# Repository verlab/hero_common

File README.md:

# HeRo: An Open Platform for Robotics Research and Education
<p align="justify">
Welcome to the HeRo project! This initiative introduces an innovative platform tailored for swarm robotics applications. It boasts affordability, ease of assembly using readily available components, and seamless integration with the industry-standard ROS (Robot Operating System). Our robotic platform is fully open-source, featuring a 3D-printed body coupled with open-source software. Within this repository, you'll discover a comprehensive range of ROS packages, firmware, simulations, examples, as well as additional resources such as CAD files, 3D models, schematics, and more.
</p>

For more in-depth information, please visit our documentation page [here](https://verlab.github.io/hero_common/).

## Authors

## Contributing
We welcome and appreciate contributions from the community. If you have ideas, bug fixes, or enhancements you'd like to propose, please feel free to open an issue or submit a pull request. Together, we can make HeRo an even better platform for robotics enthusiasts and researchers.

Thank you 🙏 to all our contributors!

## License
<br />This work is licensed under a <a rel="license" href="http://creativecommons.org/licenses/by-nc-nd/4.0/">Creative Commons Attribution-NonCommercial-ShareALike 4.0 International License</a>.

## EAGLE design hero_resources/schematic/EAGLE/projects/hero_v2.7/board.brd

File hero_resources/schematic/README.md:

# HeRo: An Open Platform for Robotics Research and Education

This project contributes to an open source ROS-based framework for swarm robotics. We propose an low cost, high availability swarm system that could be printed and assembled multiple times without special knowledge or hardware skills.

# Authors:
- [Paulo Rezeck](https://github.com/rezeck)
- [Maurício Ferrari](https://github.com/mauferrari)

# PCB Manufacturer

If you intend to maker the PCB by yourself, see the PCB version 2.1. These versions are simplified to make easy to developed it.

Case you intend to order the PCB from a professional manufacturer, look for the most recent version.

# Version Description

## v2.1
- Uses pinholes as vias, since it is dificult to produce vias in homemade PCB.
- Fix inconsistency 

## v2.3
- Change pinholes to vias, since we intent to order this board from PCB manufacturer.
- Fix motor conectors position

## v2.4
- Added battery charge module (TP4056)
- Update silk

## v2.5
- Change darlington-pair to mosfet

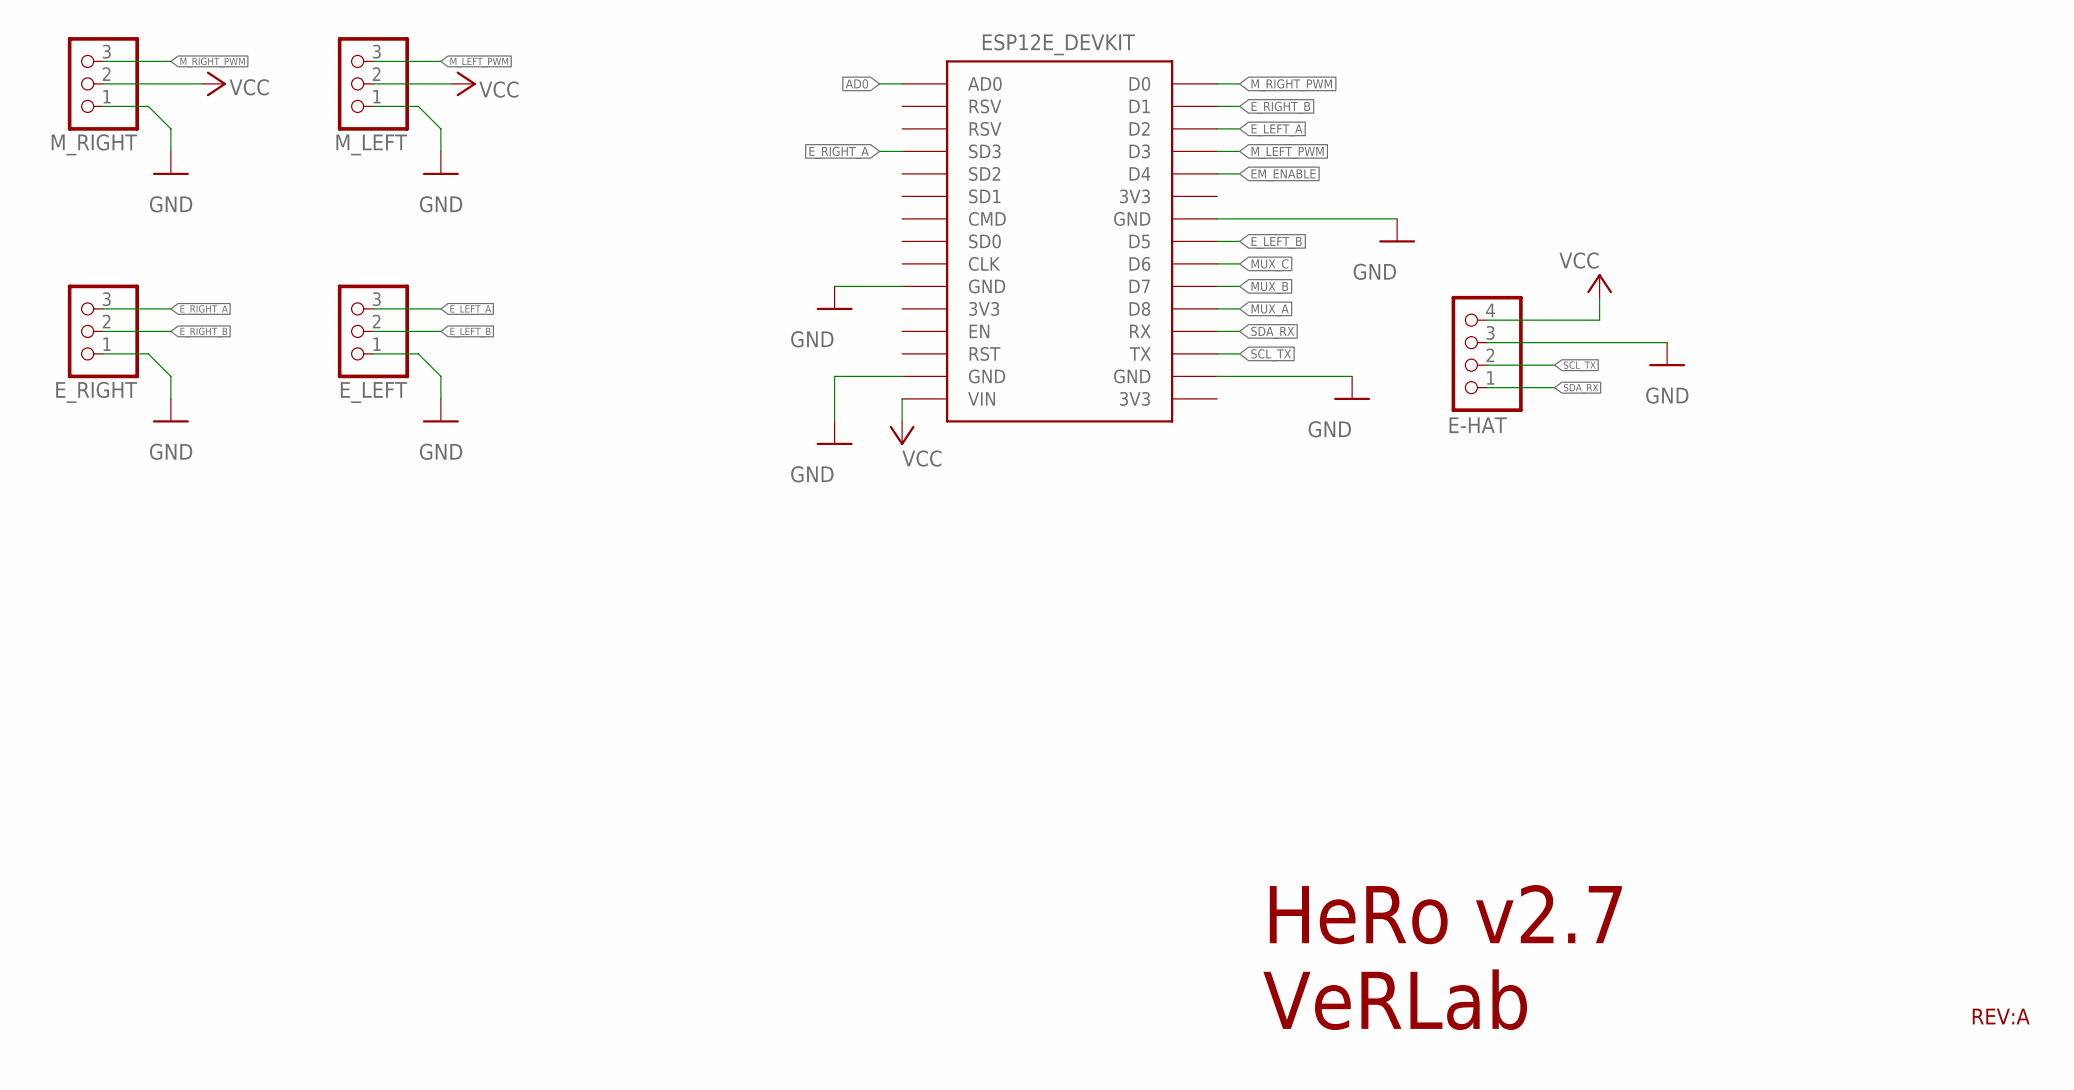
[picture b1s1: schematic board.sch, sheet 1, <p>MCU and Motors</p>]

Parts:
E-HAT: PINHD-1X4; 1X04
ESP-12E: ESP12E_DEVKIT
E_LEFT: PINHD-1X3; 1X03
E_RIGHT: PINHD-1X3; 1X03
M_LEFT: PINHD-1X3; 1X03
M_RIGHT: PINHD-1X3; 1X03

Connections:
AD0: ESP-12E.AD0; also elsewhere on the board
EM_ENABLE: ESP-12E.D4; also elsewhere on the board
E_LEFT_A: ESP-12E.D2, E_LEFT.3
E_LEFT_B: ESP-12E.D5, E_LEFT.2
E_RIGHT_A: ESP-12E.SD3, E_RIGHT.3
E_RIGHT_B: ESP-12E.D1, E_RIGHT.2
GND: E-HAT.3, ESP-12E.GND@0 (GND), ESP-12E.GND@1 (GND), ESP-12E.GND@2 (GND), ESP-12E.GND@3 (GND), E_LEFT.1, E_RIGHT.1, M_LEFT.1, M_RIGHT.1; also elsewhere on the board
MUX_A: ESP-12E.D8; also elsewhere on the board
MUX_B: ESP-12E.D7; also elsewhere on the board
MUX_C: ESP-12E.D6; also elsewhere on the board
M_LEFT_PWM: ESP-12E.D3, M_LEFT.3
M_RIGHT_PWM: ESP-12E.D0, M_RIGHT.3
SCL_TX: E-HAT.2, ESP-12E.TX
SDA_RX: E-HAT.1, ESP-12E.RX

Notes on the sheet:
HeRo v2.7 VeRLab
REV:A

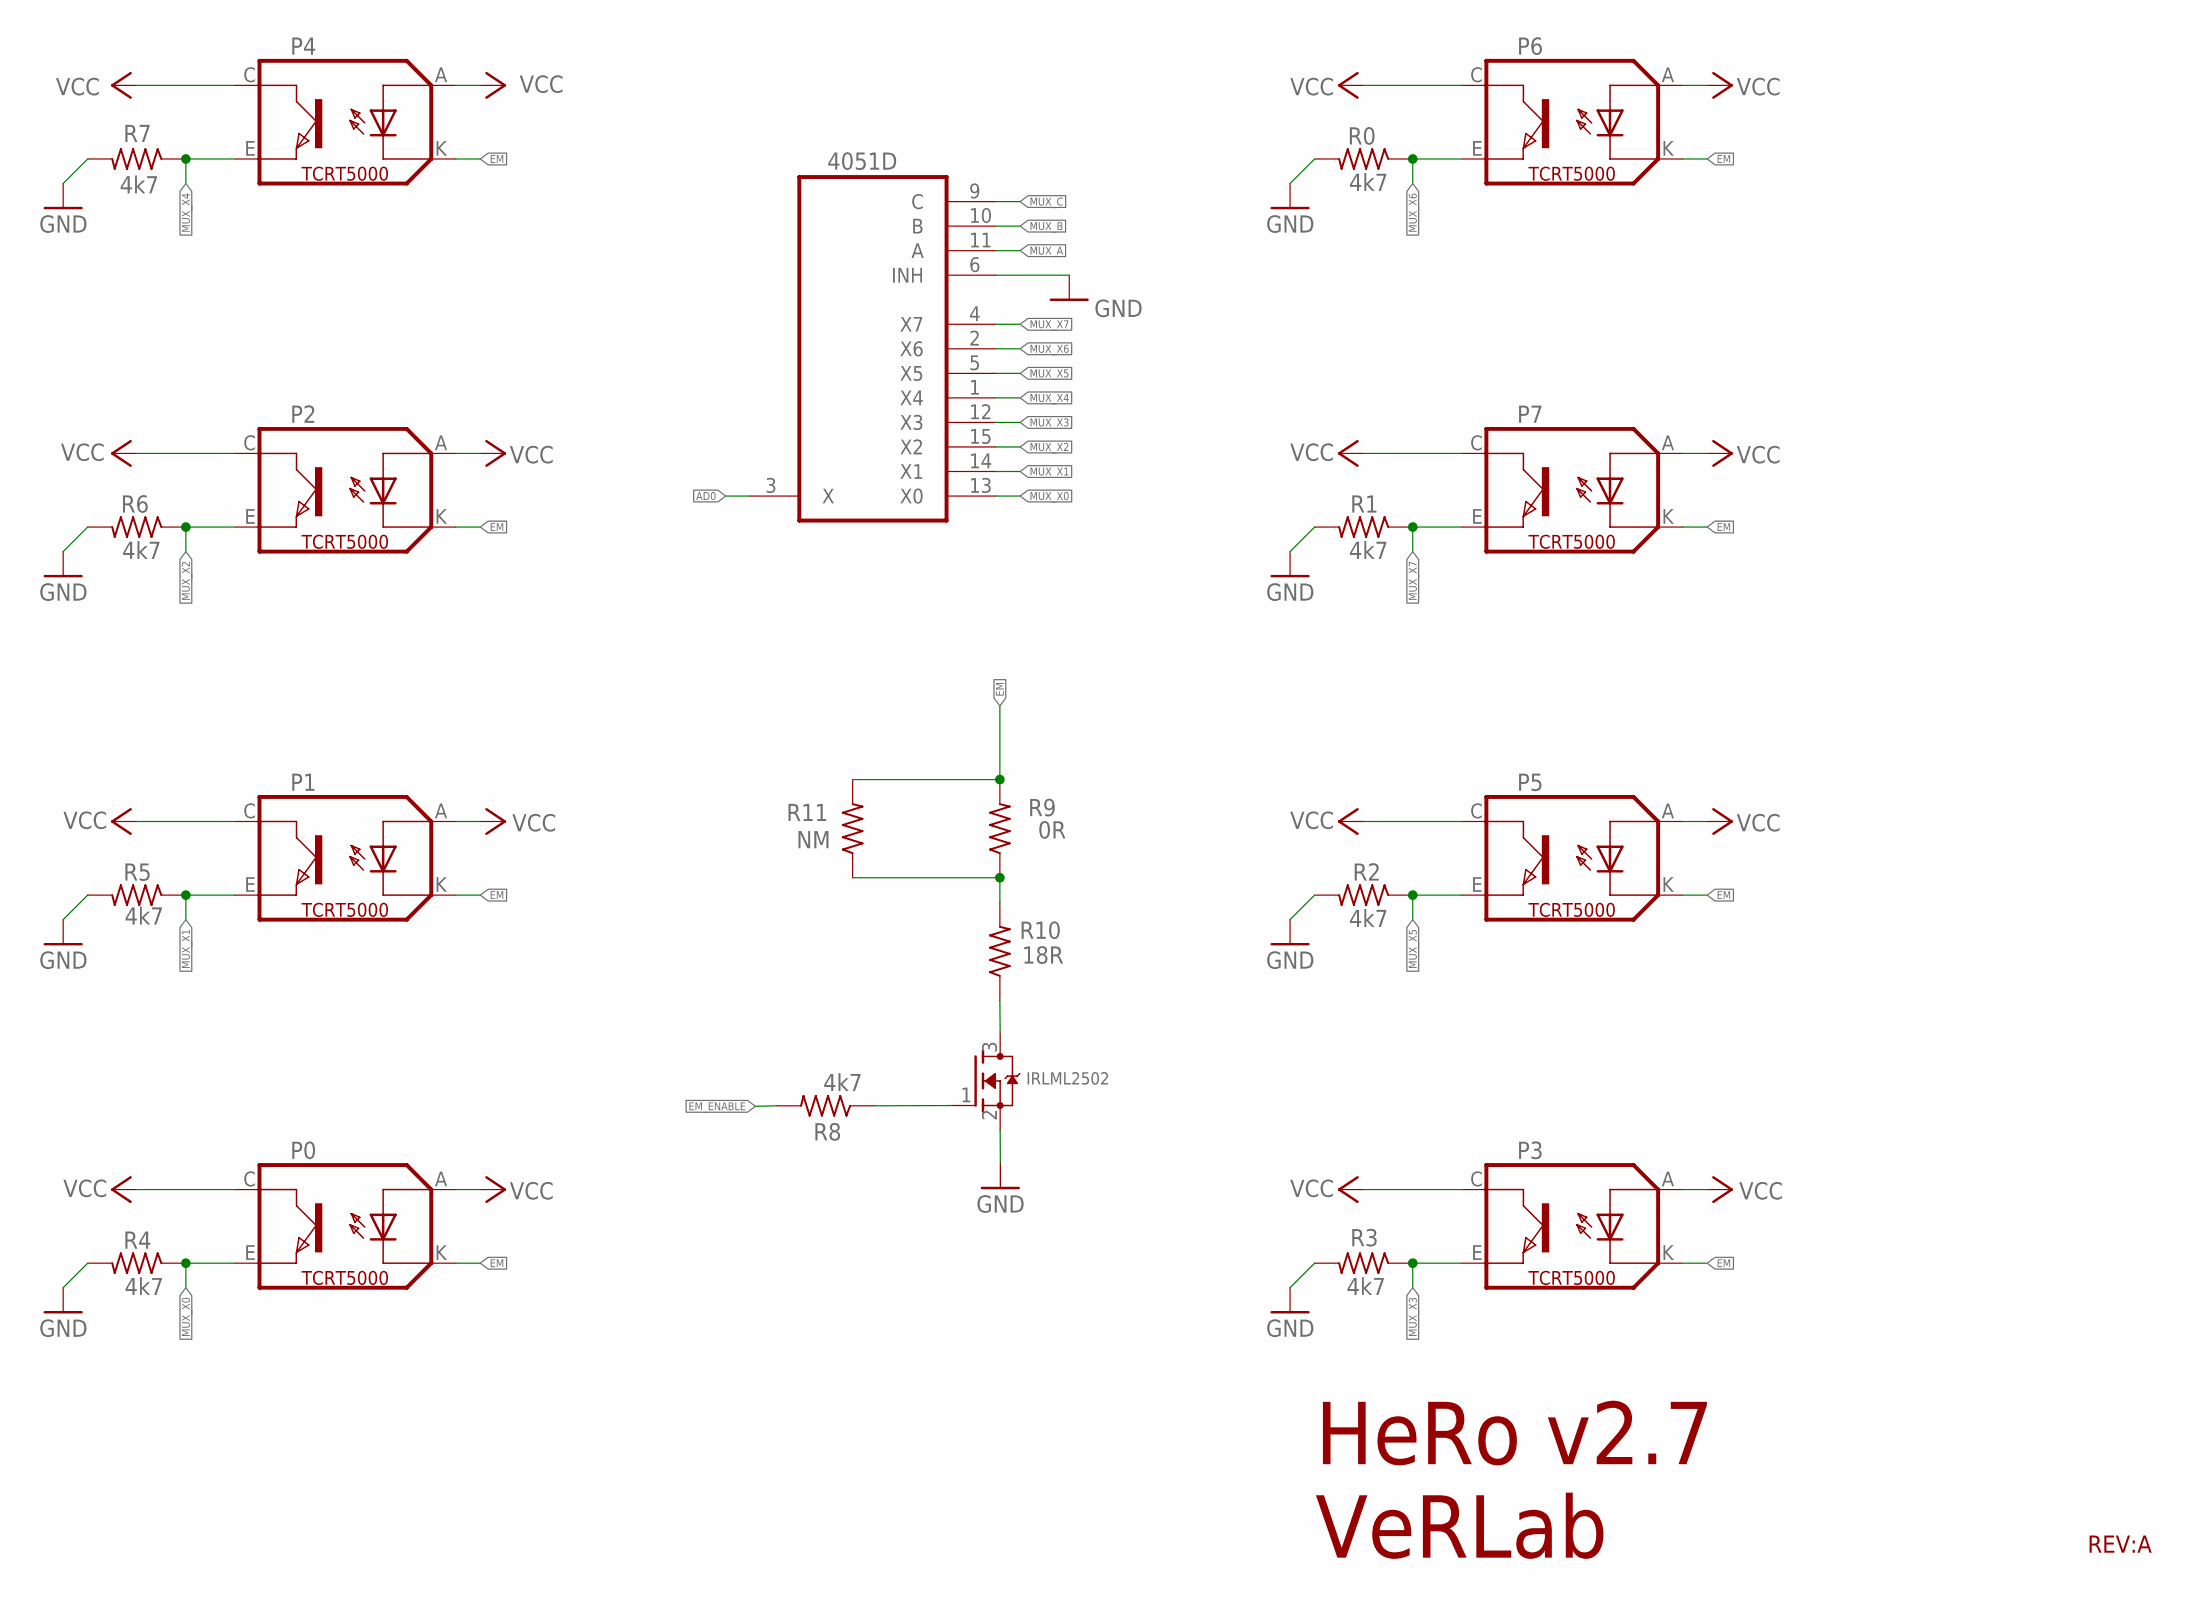
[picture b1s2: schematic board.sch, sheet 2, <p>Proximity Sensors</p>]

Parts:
IRLML2502: MOSFET-NREFLOW; SOT23
MUX: 4051D; SO16
P0, P1, P2, P3, P4, P5, P6, P7: TCRT5000
R0, R1, R2, R3, R4, R5, R6, R7: 4k7; M0805
R8: 4k7; R0805
R9: 0R; R0805
R10: 18R; R0805
R11: NM; R0805

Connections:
AD0: MUX.3 (X); also elsewhere on the board
EM: P0.K (CATHODE), P1.K (CATHODE), P2.K (CATHODE), P3.K (CATHODE), P4.K (CATHODE), P5.K (CATHODE), P6.K (CATHODE), P7.K (CATHODE), R9.2, R11.2
EM_ENABLE: R8.2; also elsewhere on the board
GND: IRLML2502.2 (S), MUX.6 (INH), MUX.7 (VEE), MUX.8 (GND), R0.2, R1.2, R2.2, R3.2, R4.2, R5.2, R6.2, R7.2; also elsewhere on the board
MUX_A: MUX.11 (A); also elsewhere on the board
MUX_B: MUX.10 (B); also elsewhere on the board
MUX_C: MUX.9 (C); also elsewhere on the board
MUX_X0: MUX.13 (X0), P0.E (EMITTER), R4.1
MUX_X1: MUX.14 (X1), P1.E (EMITTER), R5.1
MUX_X2: MUX.15 (X2), P2.E (EMITTER), R6.1
MUX_X3: MUX.12 (X3), P3.E (EMITTER), R3.1
MUX_X4: MUX.1 (X4), P4.E (EMITTER), R7.1
MUX_X5: MUX.5 (X5), P5.E (EMITTER), R2.1
MUX_X6: MUX.2 (X6), P6.E (EMITTER), R0.1
MUX_X7: MUX.4 (X7), P7.E (EMITTER), R1.1
unnamed: IRLML2502.3 (D), R10.1
unnamed: R9.1, R10.2, R11.1
unnamed: IRLML2502.1 (G), R8.1

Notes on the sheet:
HeRo v2.7 VeRLab
REV:A

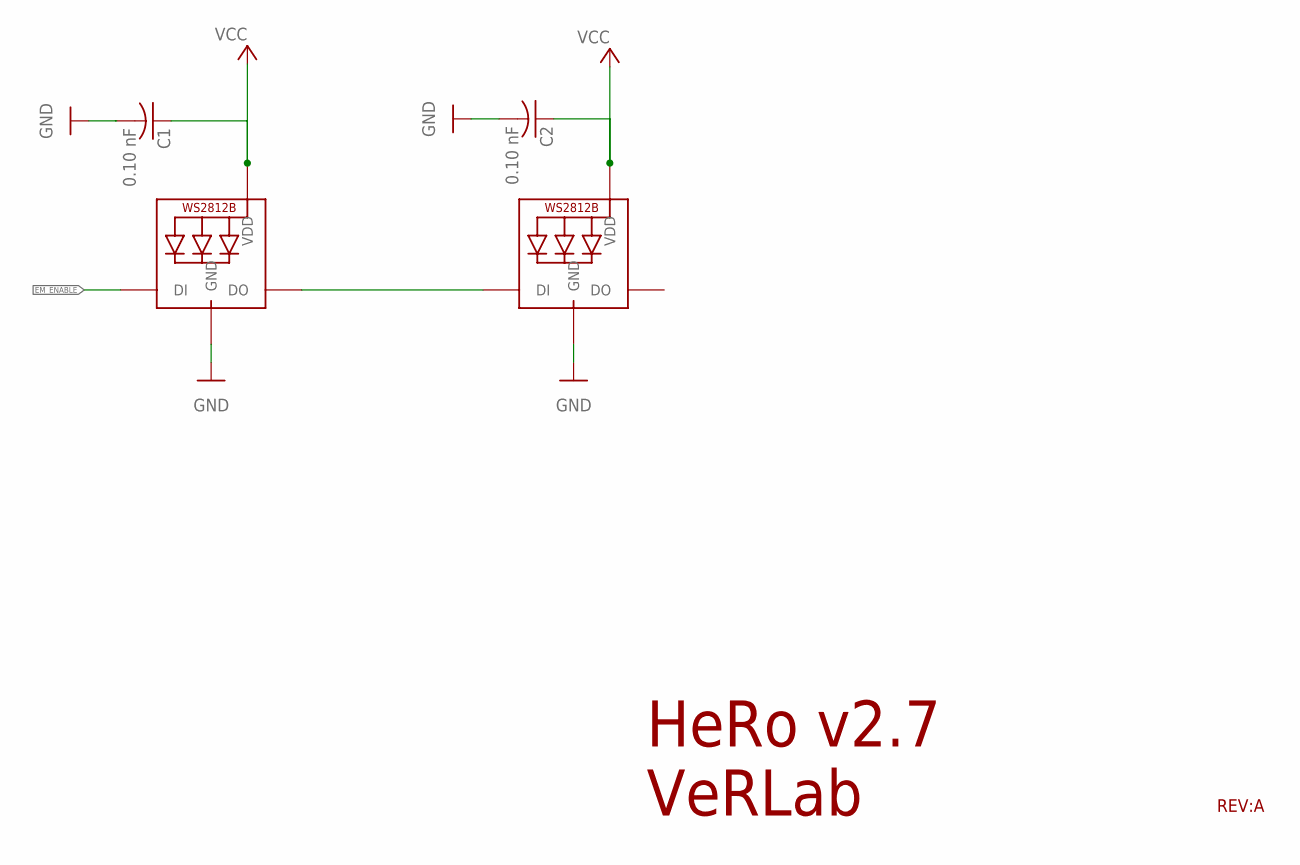
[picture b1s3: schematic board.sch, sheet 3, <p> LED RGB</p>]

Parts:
C1, C2: 0.10 nF; C0603
LED0, LED1: WS2812B5050; WS2812B

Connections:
EM_ENABLE: LED0.4-DIN (DI); also elsewhere on the board
GND: C1.2, C2.2, LED0.3-GND (GND), LED1.3-GND (GND); also elsewhere on the board
WS_OUT: LED0.2-DOUT (DO), LED1.4-DIN (DI)

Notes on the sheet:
HeRo v2.7 VeRLab
REV:A

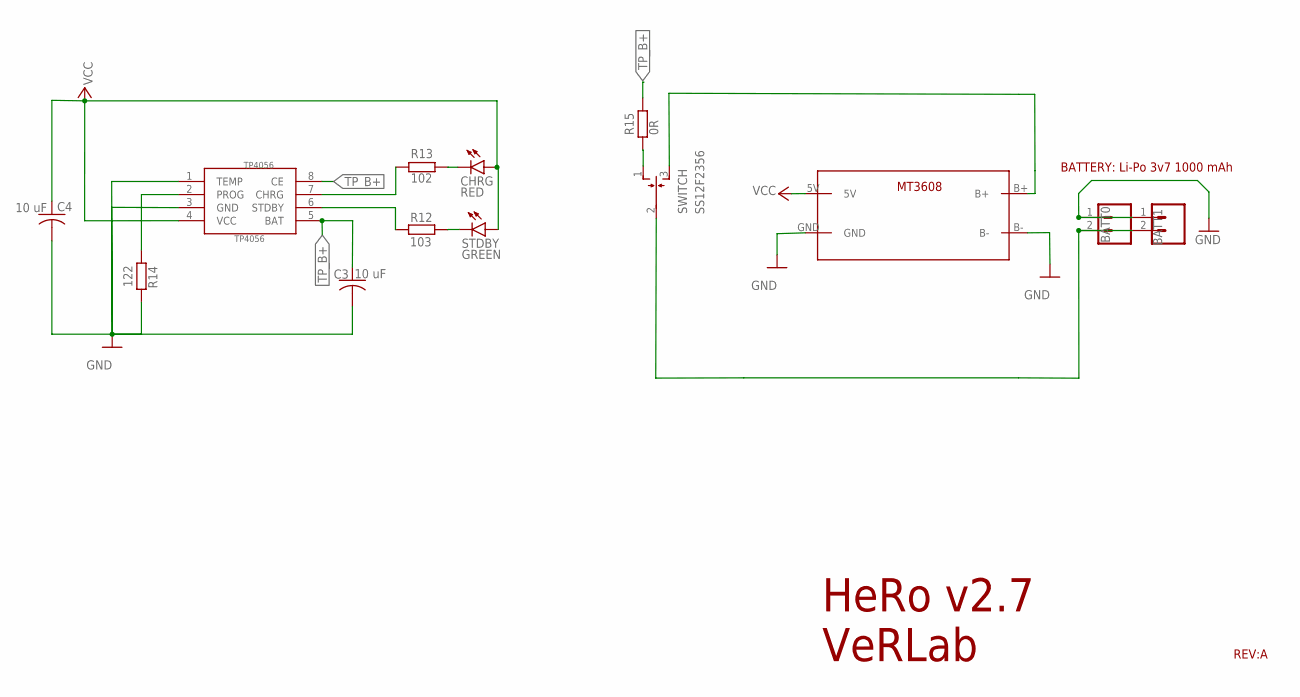
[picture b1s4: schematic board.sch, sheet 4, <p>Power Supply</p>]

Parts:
BATT0, BATT1: CONN_02JST-PTH-2; JST-2-PTH
C3, C4: 10 uF; C0603
CHRG: RED; SML0805
MT3608: MT3608
R12: 103; R0805
R13: 102; R0805
R14: 122; R0603
R15: 0R; R0805
STDBY: GREEN; SML0805
SWITCH: SS12F2356; HH3T90
TP4056: TP4056; SOP-8

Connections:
B+: MT3608.B+, SWITCH.3 (S)
CHRG: R13.1, TP4056.7 (CHRG)
GND: BATT0.1, BATT1.1, C3.2, C4.2, MT3608.B-, MT3608.GND, R14.1, TP4056.1 (TEMP), TP4056.3 (GND); also elsewhere on the board
unnamed: BATT0.2, BATT1.2, SWITCH.2
unnamed: CHRG.C, R13.2
unnamed: R12.2, STDBY.C
PROG: R14.2, TP4056.2 (PROG)
STDBY: R12.1, TP4056.6 (STDBY)
TP_BS: R15.1, SWITCH.1 (O)

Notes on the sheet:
HeRo v2.7 VeRLab
BATTERY: Li-Po 3v7 1000 mAh
REV:A

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
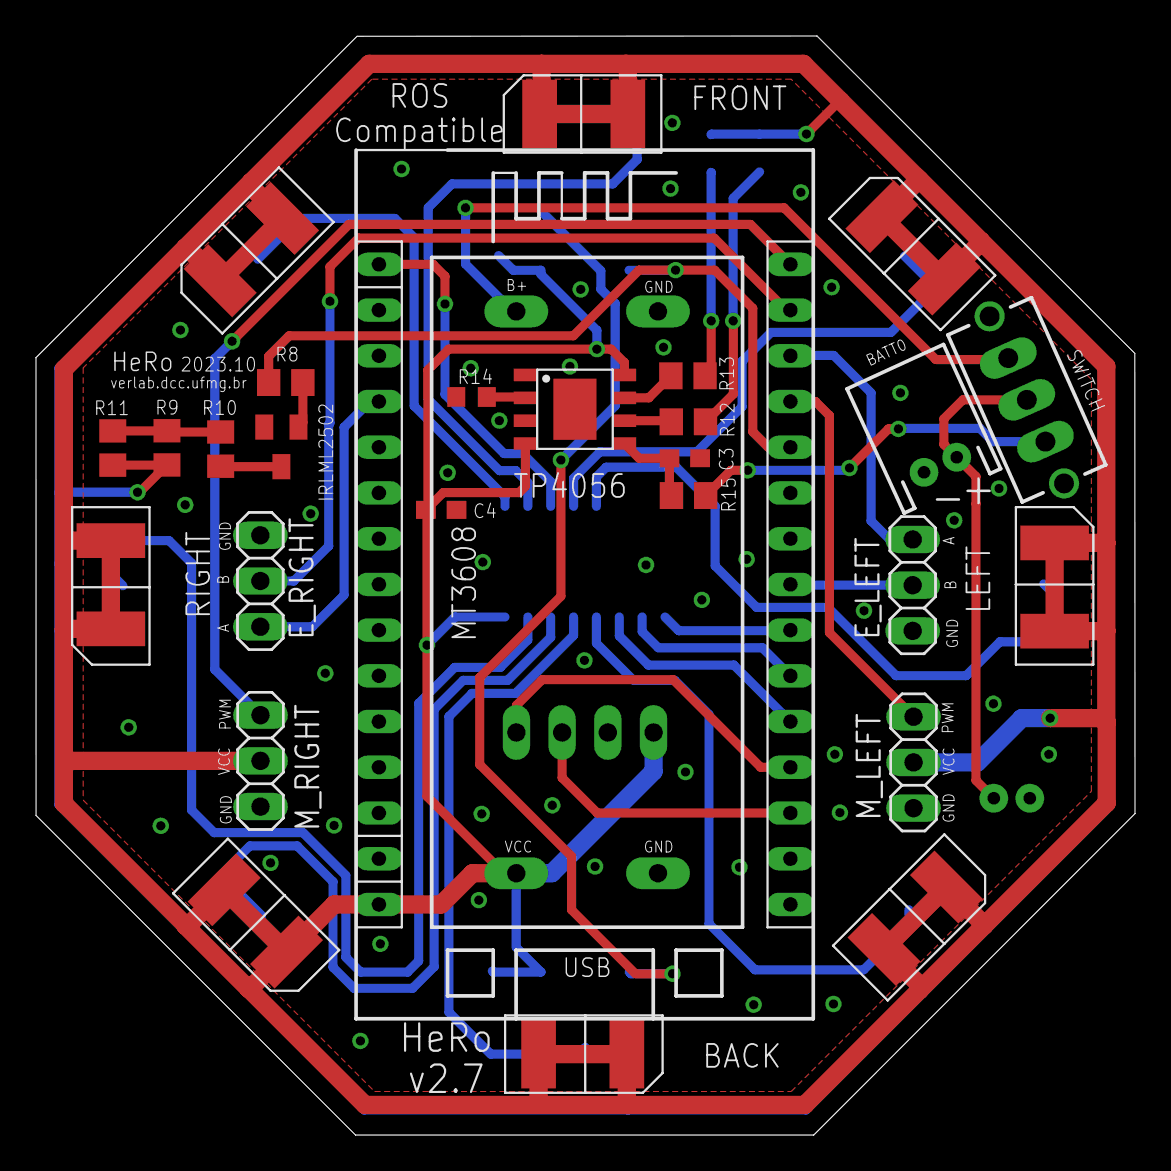
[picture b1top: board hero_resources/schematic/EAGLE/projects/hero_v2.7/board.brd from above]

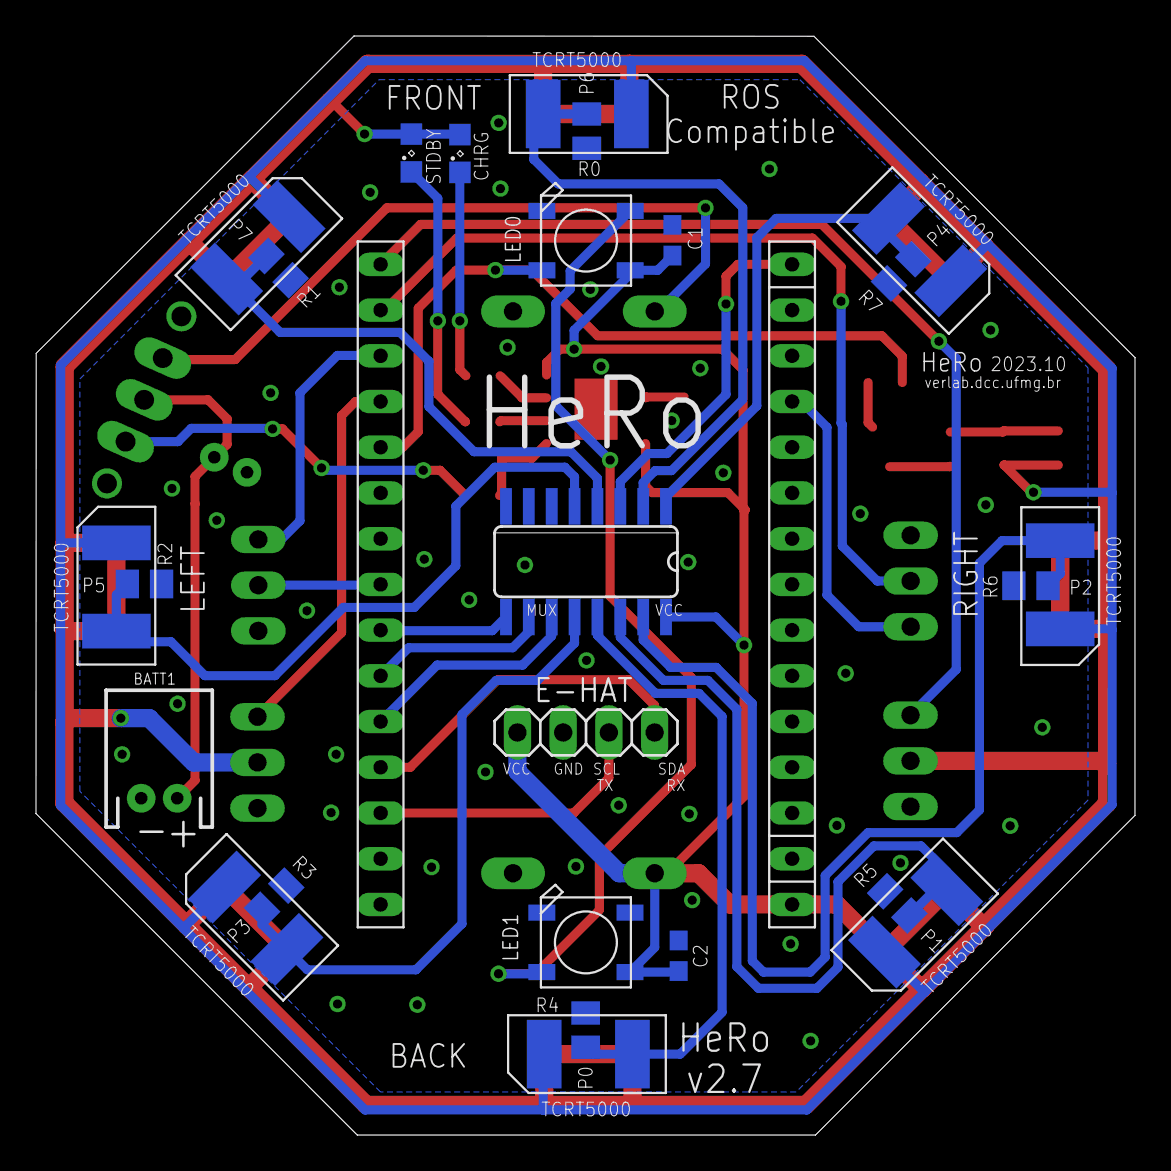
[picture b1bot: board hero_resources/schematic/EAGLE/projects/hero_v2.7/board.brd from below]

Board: 2 copper layers, 61.1 x 61.1 mm, 45 parts (25 on the bottom side), 37 nets.

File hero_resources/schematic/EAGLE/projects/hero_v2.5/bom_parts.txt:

Partlist exported from /home/rezeck/EAGLE/projects/hero_v2.5/board.sch at 6/5/19 10:48 AM

Part      Value         Device         Package       Description                  SPICEPREFIX
BATT                    PINHD-1X2      1X02          PIN HEADER                              
C1        0.10 nF       C-USC0603      C0603         CAPACITOR, American symbol              
C2        0.10 nF       C-USC0603      C0603         CAPACITOR, American symbol              
C3        10 uF         C-USC0603      C0603         CAPACITOR, American symbol              
C4        10 uF         C-USC0603      C0603         CAPACITOR, American symbol              
CHRG                    LEDSML0805     SML0805       LED                                     
E_LEFT                  PINHD-1X3      1X03          PIN HEADER                              
E_RIGHT                 PINHD-1X3      1X03          PIN HEADER                              
I2C|UART                PINHD-1X4      1X04          PIN HEADER                              
IC1       TP4056        TP4056         SOP-8                                      X          
IC2       4051D         4051D          SO16          8-channel ANALOG MULTIPLEXER            
IRLML2502               MOSFET-NREFLOW SOT23         N-Channel Mosfet                        
LED0      WS2812B5050   WS2812B5050    WS2812B                                               
LED1      WS2812B5050   WS2812B5050    WS2812B                                               
M_LEFT                  PINHD-1X3      1X03          PIN HEADER                              
M_RIGHT                 PINHD-1X3      1X03          PIN HEADER                              
OS1                     STEPUP         STEPUP                                                
P0                      TCRT5000       TCRT5000                                              
P1                      TCRT5000       TCRT5000                                              
P2                      TCRT5000       TCRT5000                                              
P3                      TCRT5000       TCRT5000                                              
P4                      TCRT5000       TCRT5000                                              
P5                      TCRT5000       TCRT5000                                              
P6                      TCRT5000       TCRT5000                                              
P7                      TCRT5000       TCRT5000                                              
R0        4k7           R-US_M0805     M0805         RESISTOR, American symbol               
R1        4k7           R-US_M0805     M0805         RESISTOR, American symbol               
R2        4k7           R-US_M0805     M0805         RESISTOR, American symbol               
R3        4k7           R-US_M0805     M0805         RESISTOR, American symbol               
R4        4k7           R-US_M0805     M0805         RESISTOR, American symbol               
R5        4k7           R-US_M0805     M0805         RESISTOR, American symbol               
R6        4k7           R-US_M0805     M0805         RESISTOR, American symbol               
R7        4k7           R-US_M0805     M0805         RESISTOR, American symbol               
R8        4k7           R-US_R0805     R0805         RESISTOR, American symbol    R          
R9        0 R           R-US_R0805     R0805         RESISTOR, American symbol    R          
R10       18 R          R-US_R0805     R0805         RESISTOR, American symbol    R          
R11       NM            R-US_R0805     R0805         RESISTOR, American symbol    R          
R12       102           R-EU_R0805     R0805         RESISTOR, European symbol               
R13       102           R-EU_R0805     R0805         RESISTOR, European symbol               
R14       122           R-EU_R0603     R0603         RESISTOR, European symbol               
STDBY                   LEDSML0805     SML0805       LED                                     
SWITCH    TL37YO        TL37YO         TL3XYO        TINY SWITCH MOM OFF MOM                 
U$1       ESP12E_DEVKIT ESP12E_DEVKIT  ESP12E_DEVKIT ESP12E DEVKIT BOARD

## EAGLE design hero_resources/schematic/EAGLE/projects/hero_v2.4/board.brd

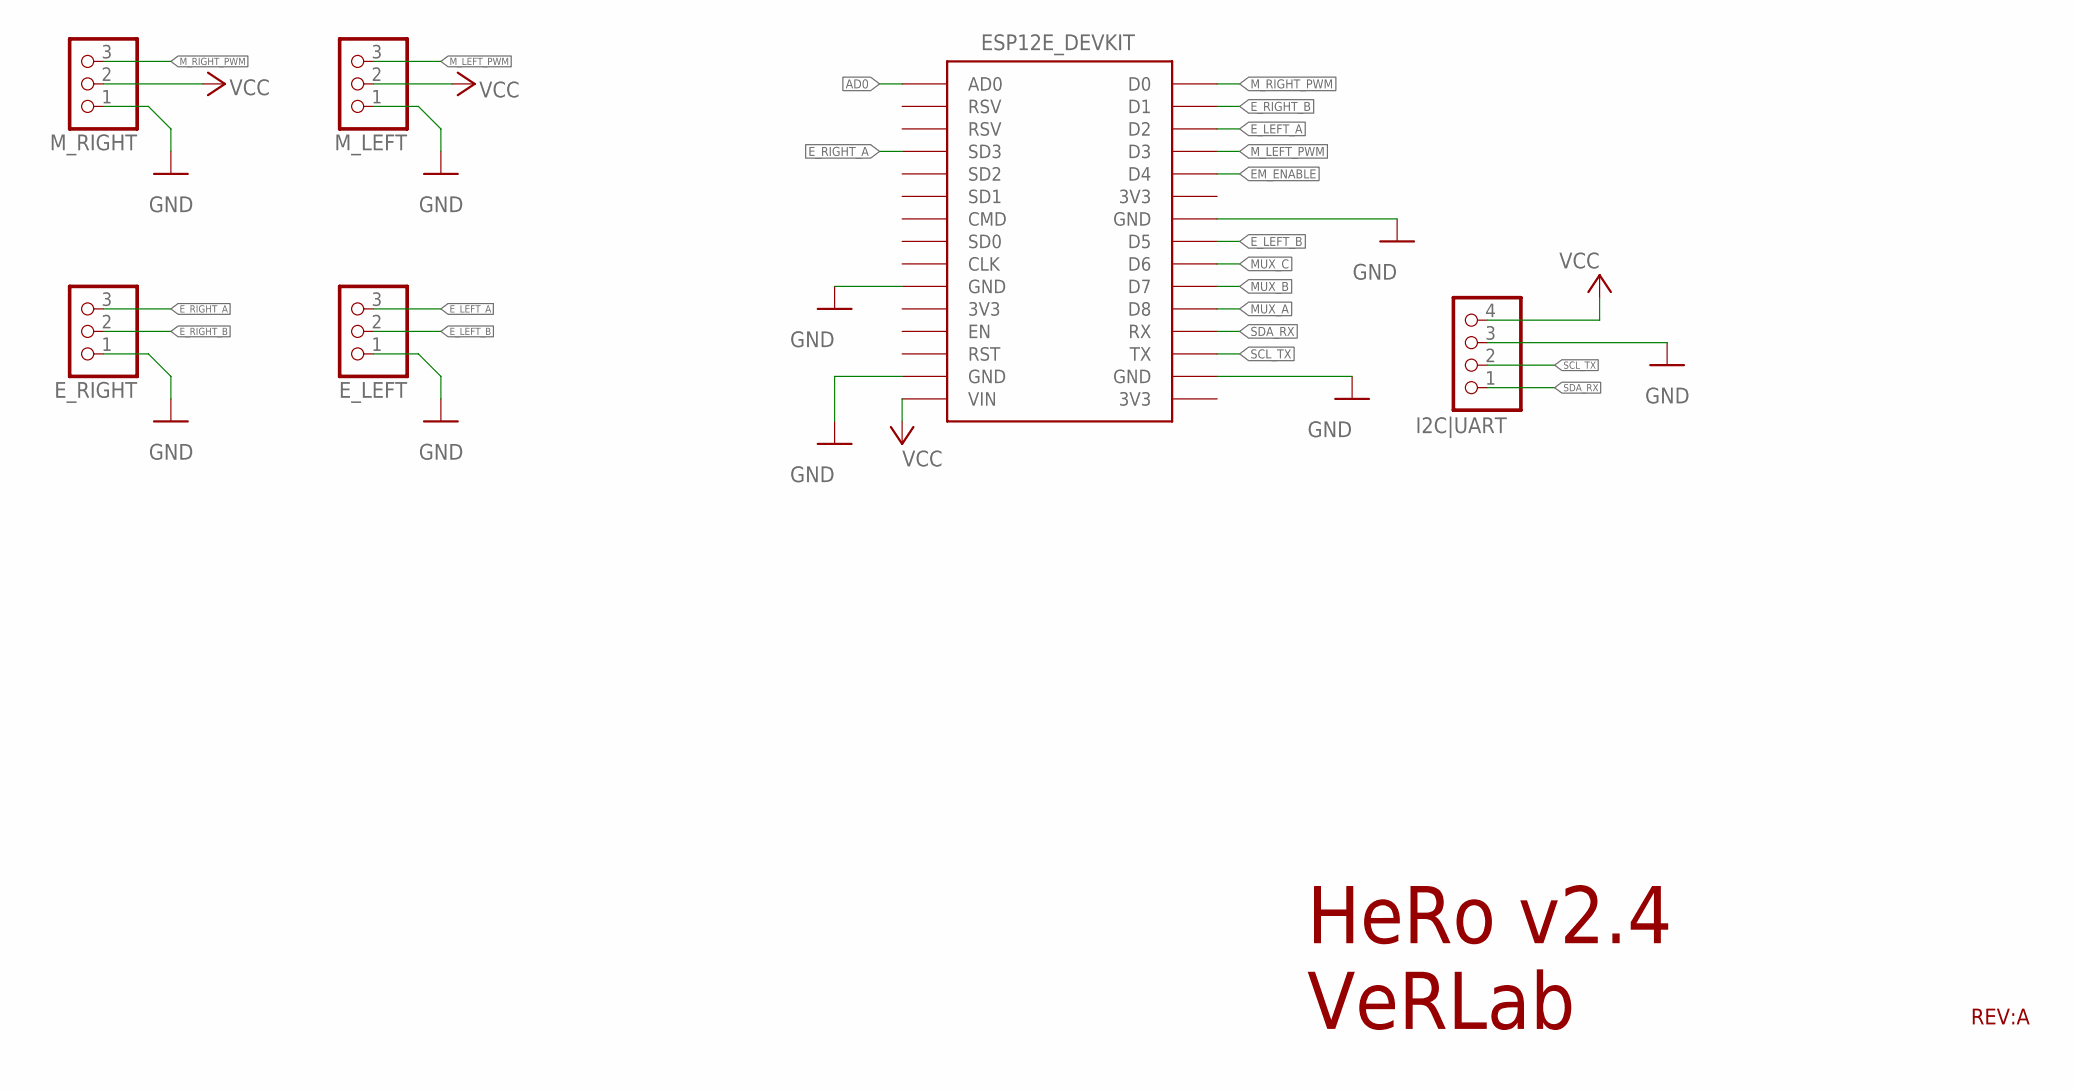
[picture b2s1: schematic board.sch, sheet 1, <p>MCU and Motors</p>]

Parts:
E_LEFT: PINHD-1X3; 1X03
E_RIGHT: PINHD-1X3; 1X03
I2C|UART: PINHD-1X4; 1X04
M_LEFT: PINHD-1X3; 1X03
M_RIGHT: PINHD-1X3; 1X03
U$1: ESP12E_DEVKIT

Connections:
AD0: U$1.AD0; also elsewhere on the board
EM_ENABLE: U$1.D4; also elsewhere on the board
E_LEFT_A: E_LEFT.3, U$1.D2
E_LEFT_B: E_LEFT.2, U$1.D5
E_RIGHT_A: E_RIGHT.3, U$1.SD3
E_RIGHT_B: E_RIGHT.2, U$1.D1
GND: E_LEFT.1, E_RIGHT.1, I2C|UART.3, M_LEFT.1, M_RIGHT.1, U$1.GND@0 (GND), U$1.GND@1 (GND), U$1.GND@2 (GND), U$1.GND@3 (GND); also elsewhere on the board
MUX_A: U$1.D8; also elsewhere on the board
MUX_B: U$1.D7; also elsewhere on the board
MUX_C: U$1.D6; also elsewhere on the board
M_LEFT_PWM: M_LEFT.3, U$1.D3
M_RIGHT_PWM: M_RIGHT.3, U$1.D0
SCL_TX: I2C|UART.2, U$1.TX
SDA_RX: I2C|UART.1, U$1.RX
VCC: I2C|UART.4, M_LEFT.2, M_RIGHT.2, U$1.VIN; also elsewhere on the board

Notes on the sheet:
HeRo v2.4 VeRLab
REV:A

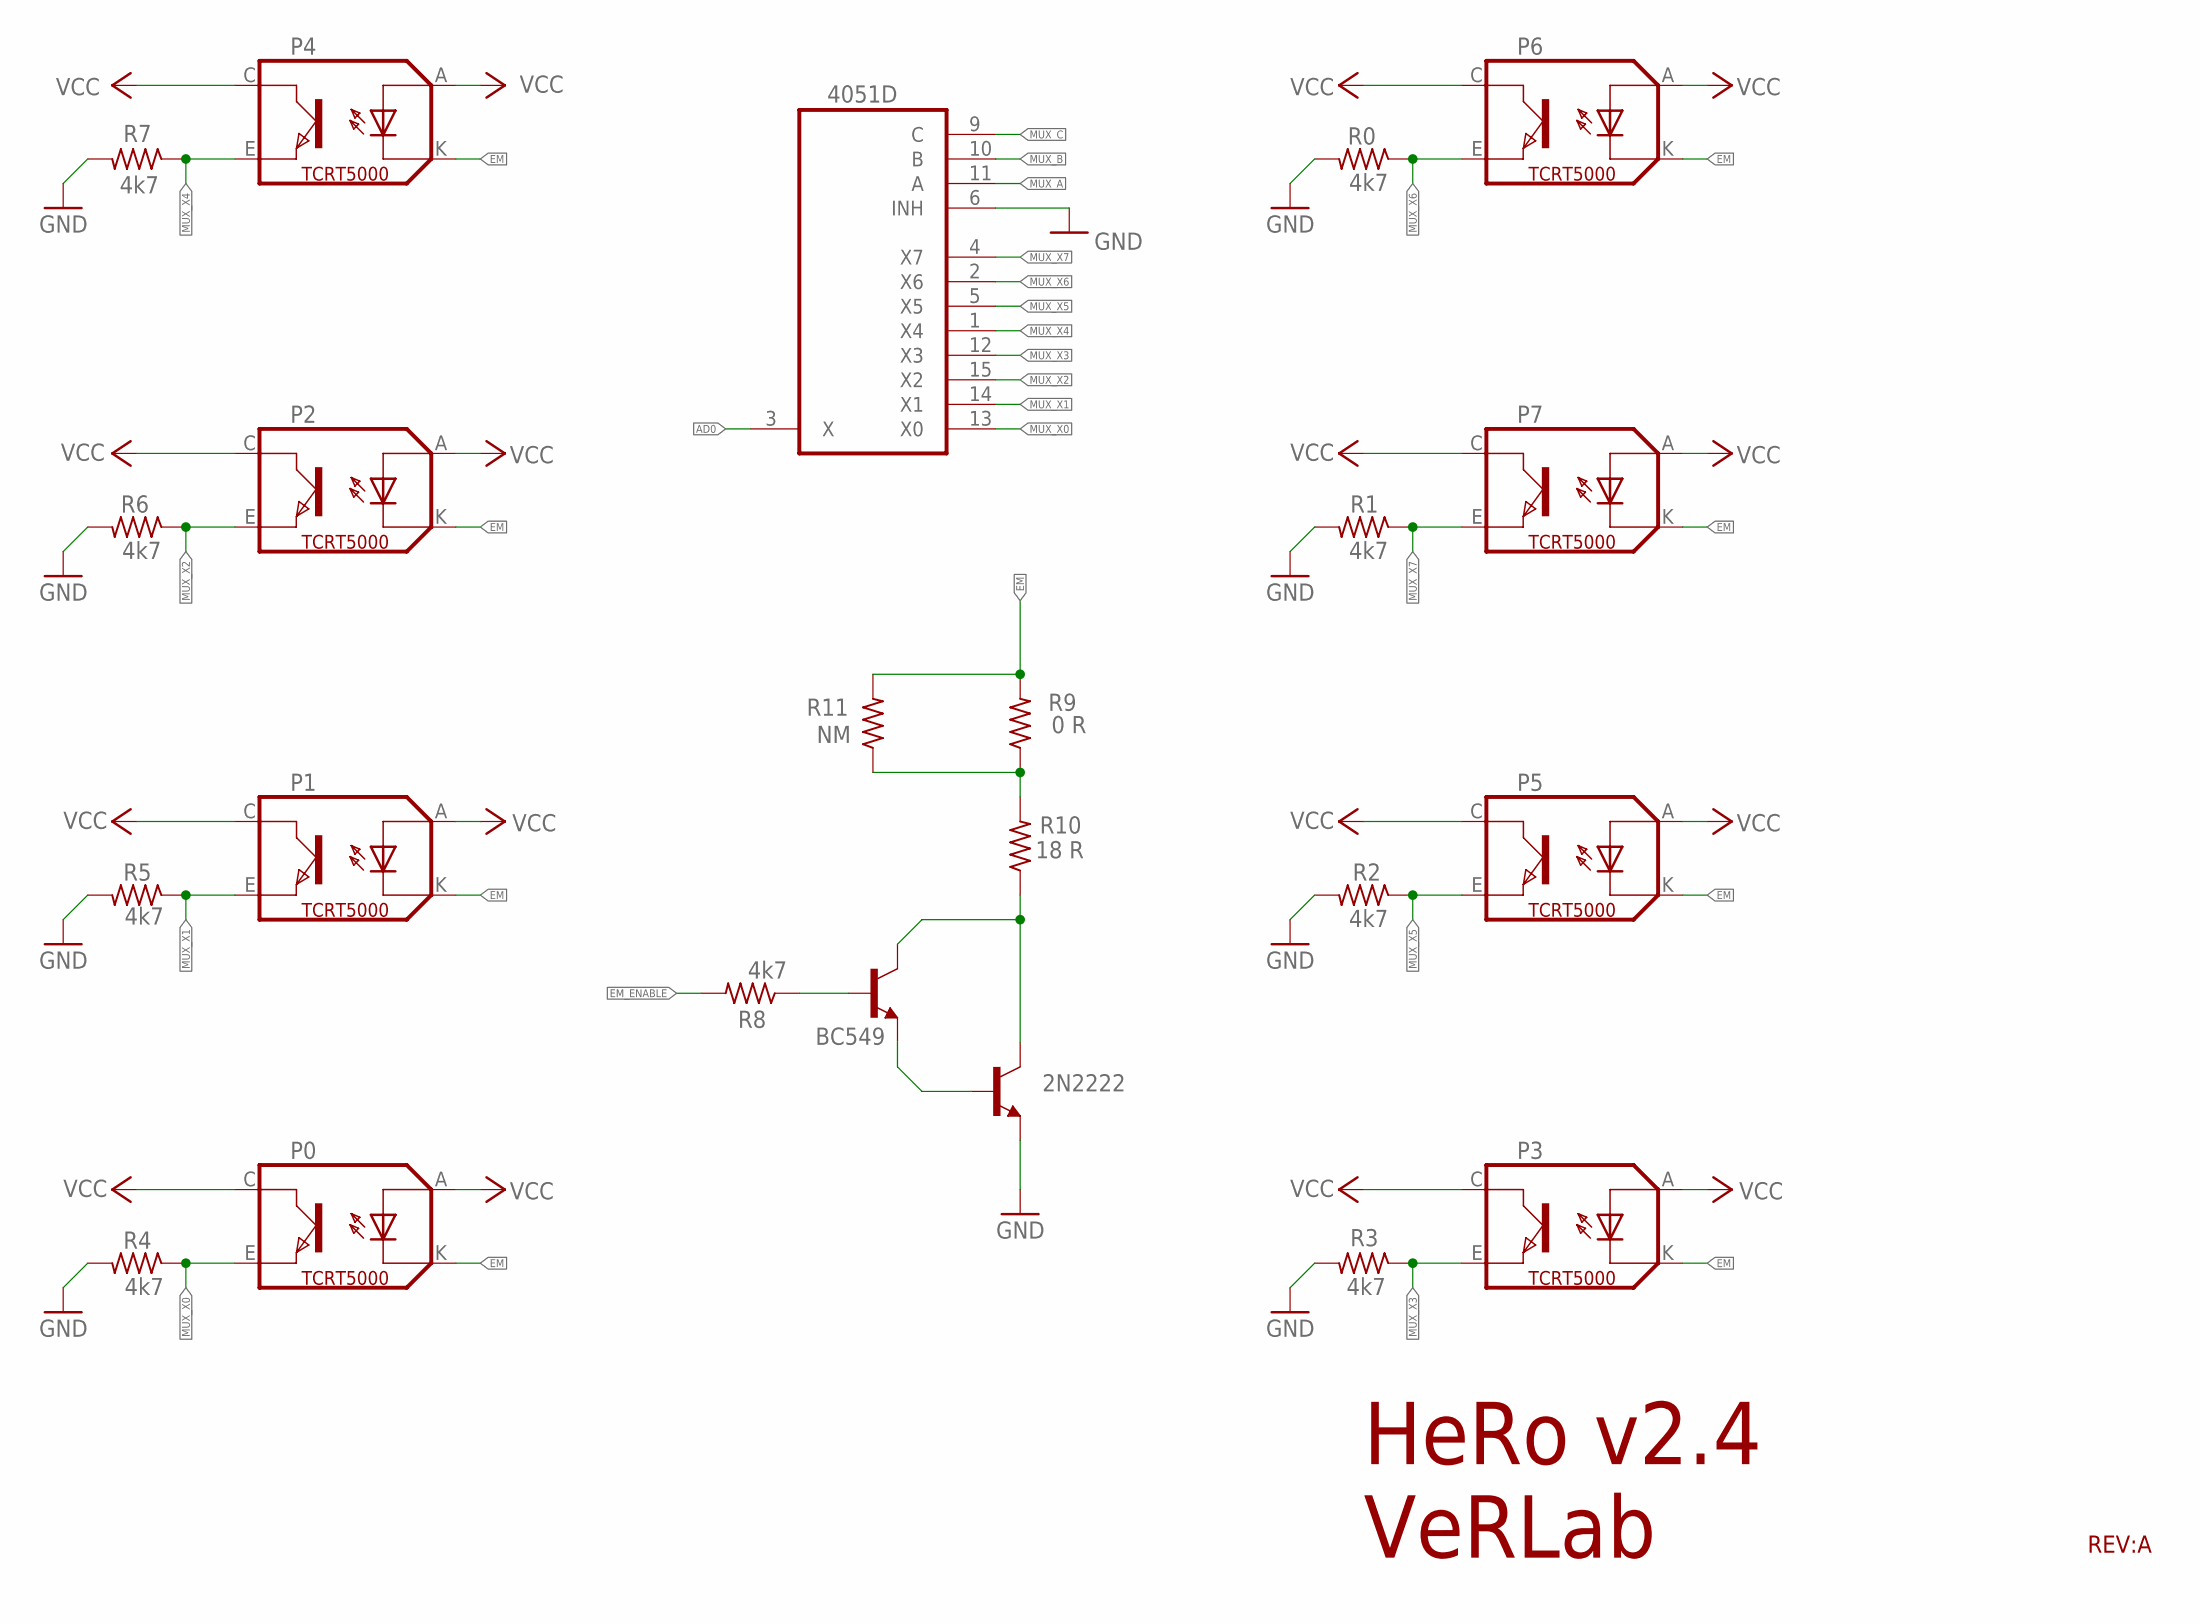
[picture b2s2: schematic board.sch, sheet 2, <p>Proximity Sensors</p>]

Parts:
BC549: BC549-NPN-TO92-CBE; TO92-CBE
IC2: 4051D; SO16
P0, P1, P2, P3, P4, P5, P6, P7: TCRT5000
R0, R1, R2, R3, R4, R5, R6, R7: 4k7; M0805
R8: 4k7; R0805
R9: 0 R; R0805
R10: 18 R; R0805
R11: NM; R0805
T5: 2N2222; TO92-EBC-OVAL

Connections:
AD0: IC2.3 (X); also elsewhere on the board
EM: P0.K (CATHODE), P1.K (CATHODE), P2.K (CATHODE), P3.K (CATHODE), P4.K (CATHODE), P5.K (CATHODE), P6.K (CATHODE), P7.K (CATHODE), R9.2, R11.2
EM_ENABLE: R8.2; also elsewhere on the board
EM_ENABLE_RES: BC549.B, R8.1
GND: IC2.6 (INH), IC2.8 (GND), R0.2, R1.2, R2.2, R3.2, R4.2, R5.2, R6.2, R7.2, T5.E; also elsewhere on the board
MUX_A: IC2.11 (A); also elsewhere on the board
MUX_B: IC2.10 (B); also elsewhere on the board
MUX_C: IC2.9 (C); also elsewhere on the board
MUX_X0: IC2.13 (X0), P0.E (EMITTER), R4.1
MUX_X1: IC2.14 (X1), P1.E (EMITTER), R5.1
MUX_X2: IC2.15 (X2), P2.E (EMITTER), R6.1
MUX_X3: IC2.12 (X3), P3.E (EMITTER), R3.1
MUX_X4: IC2.1 (X4), P4.E (EMITTER), R7.1
MUX_X5: IC2.5 (X5), P5.E (EMITTER), R2.1
MUX_X6: IC2.2 (X6), P6.E (EMITTER), R0.1
MUX_X7: IC2.4 (X7), P7.E (EMITTER), R1.1
unnamed: R9.1, R10.2, R11.1
unnamed: BC549.C, R10.1, T5.C
unnamed: BC549.E, T5.B
VCC: IC2.16 (VCC), P0.A (ANODE), P0.C (COLLECTOR), P1.A (ANODE), P1.C (COLLECTOR), P2.A (ANODE), P2.C (COLLECTOR), P3.A (ANODE), P3.C (COLLECTOR), P4.A (ANODE), P4.C (COLLECTOR), P5.A (ANODE), P5.C (COLLECTOR), P6.A (ANODE), P6.C (COLLECTOR), P7.A (ANODE), P7.C (COLLECTOR); also elsewhere on the board
VEE: IC2.7 (VEE)

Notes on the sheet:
HeRo v2.4 VeRLab
REV:A

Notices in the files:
parts and their libraries:
SparkFun-Connectors: Licensing: Creative Commons ShareAlike 4.0 International - https://creativecommons.org/licenses/by-sa/4.0
